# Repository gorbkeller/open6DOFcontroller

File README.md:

# open6DOFcontroller
## Gordon Keller
### 10/23/21

*** An open-source 6DOF (Degrees Of Freedom) controller. ***

This project leverages several different packages to enable 6DOF input akin to the closed-source/proprietary hardware 3D Connexion SpaceMouse.

In this original form, it combines:
* FIRMWARE: The QMK Firmware project (link) -- TBD
* ELECTRONICS: KiCAD (link)
* HARDWARE/MODELS: Autodesk Fusion360 (link), though intention to eventually port to FreeCAD.

This controller is based on hall-effect sensors. The first pass of algorithms developed to convert magnetic signals to 6DOF aren't very sophistocated and could use a major rework.
Theoretically, it can be used to control any 3D virtualized perspective/object. Eventually, I want to use it to fly the Lynchpin drone (link) in simulation and in IRL too ;)
I've included in this first installment a driver written for Fusion360 camera view control as an example useage. This is written using the Fusion360 Scripting API.

The outputs of the one-handed module are given in either XYZ-translation + WIJK-Quaternion ("pose-mode") or XYZ-translation + Roll/Pitch/Yaw ("euler-mode"). 

Some people might not like the 6DOF with one hand control, so a fork of this repo (3DOF-3DOF) should be created eventually which splits the device in two for use with both hands. This method involves less signal processing but requires multiple PCBs.

In-depth plan TBD! - gribgrob_k

[The main bodies of the V0.1 design](imgs/o6DOFc_V0.1.png)

TO-DO:
High-priority:
1. Validate first version of the flex PCB
2. Finish start-up calibration sequence
3. Port data processing to fusion script for proof-of-concept

Low-priority:
1. Port output values from example Fusion script to the dedicated MCU (arduino initially)
2. Develop QMK-side of the device

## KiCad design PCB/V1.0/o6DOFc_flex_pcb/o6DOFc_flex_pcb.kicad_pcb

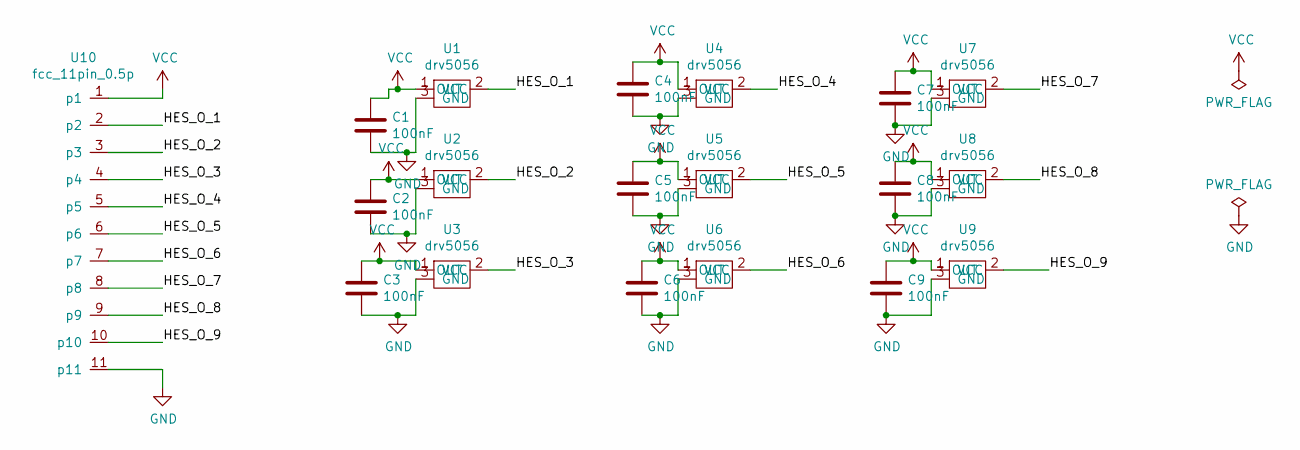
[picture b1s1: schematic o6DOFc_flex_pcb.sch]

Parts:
C1, C2, C3, C4, C5, C6, C7, C8, C9: 100nF; C_0603_1608Metric
U1, U2, U3, U4, U5, U6, U7, U8, U9: drv5056; SOT-23
U10: fcc_11pin_0.5p; ffc_11_pin_0.5_p

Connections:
/HES_O_1: U1.2 (OUT), U10.2 (p2)
/HES_O_2: U2.2 (OUT), U10.3 (p3)
/HES_O_3: U3.2 (OUT), U10.4 (p4)
/HES_O_4: U4.2 (OUT), U10.5 (p5)
/HES_O_5: U5.2 (OUT), U10.6 (p6)
/HES_O_6: U6.2 (OUT), U10.7 (p7)
/HES_O_7: U7.2 (OUT), U10.8 (p8)
/HES_O_8: U8.2 (OUT), U10.9 (p9)
/HES_O_9: U9.2 (OUT), U10.10 (p10)
GND: C1.2, C2.2, C3.2, C4.2, C5.2, C6.2, C7.2, C8.2, C9.2, U1.3 (GND), U2.3 (GND), U3.3 (GND), U4.3 (GND), U5.3 (GND), U6.3 (GND), U7.3 (GND), U8.3 (GND), U9.3 (GND), U10.11 (p11)
VCC: C1.1, C2.1, C3.1, C4.1, C5.1, C6.1, C7.1, C8.1, C9.1, U1.1 (VCC), U2.1 (VCC), U3.1 (VCC), U4.1 (VCC), U5.1 (VCC), U6.1 (VCC), U7.1 (VCC), U8.1 (VCC), U9.1 (VCC), U10.1 (p1)

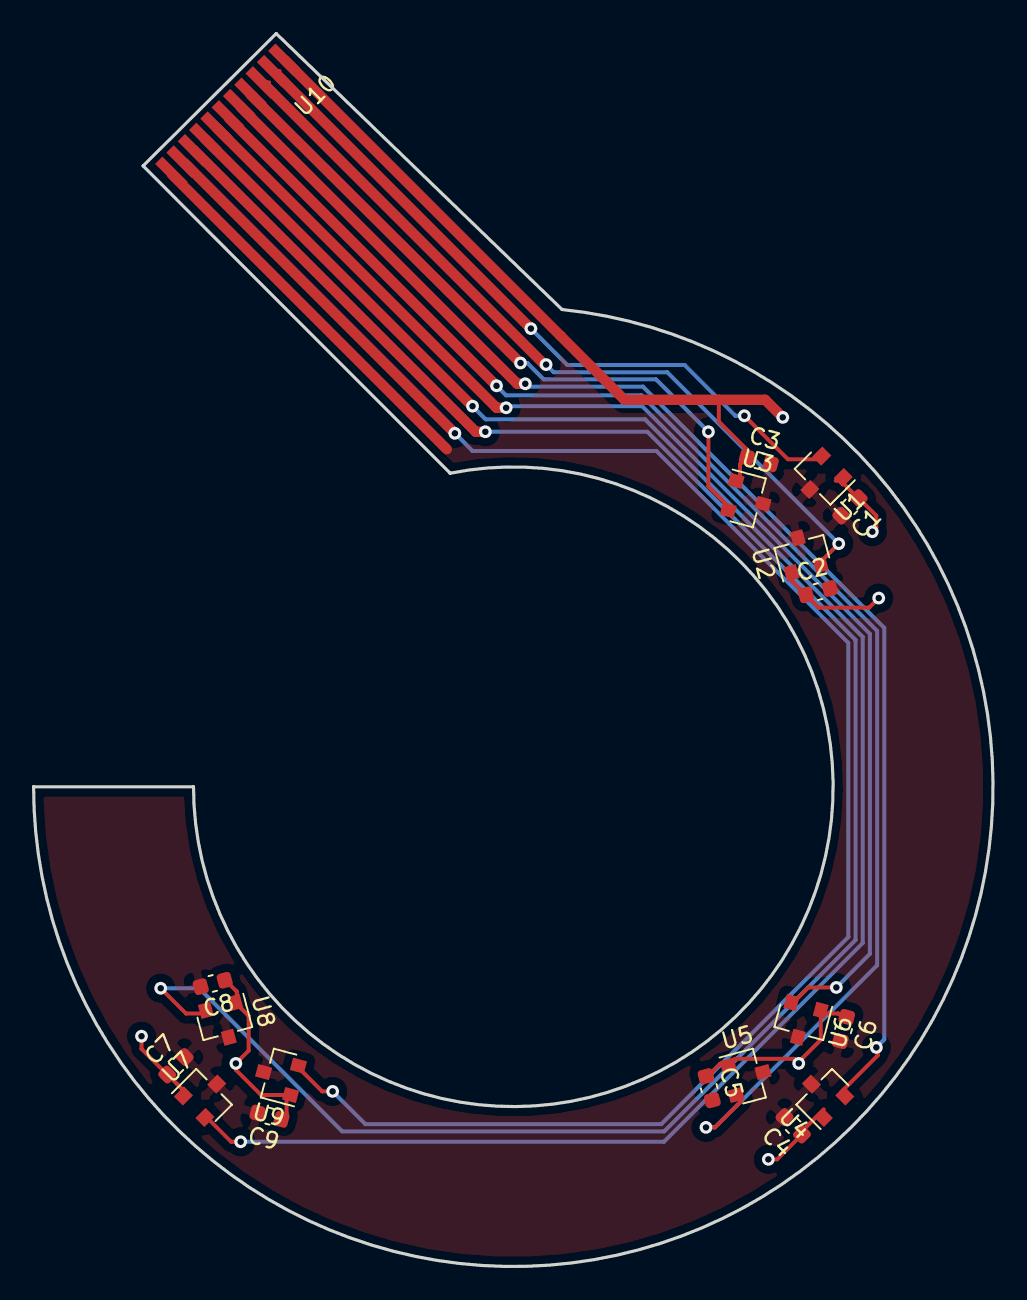
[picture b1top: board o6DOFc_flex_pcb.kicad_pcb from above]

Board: 2 copper layers, 60.0 x 77.1 mm, 19 parts (0 on the bottom side), 11 nets.

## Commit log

2021-10-23 Added details to the READMEw
2021-10-23 Added Fusion360 example driver
2021-10-23 Added image of the basic bodies to the readme
2021-10-23 Added the V0.0 stls
2021-10-23 Fixed link to image
2021-10-23 Added v0.1 STLs
2021-10-23 Added super basic script for reading out values from HEFs
2021-10-23 made the readme less obnoxious
2021-10-23 Uploading initial KiCAD project
2021-10-23 Moved calibration and testing files to a new direcotry
2021-10-23 added the Fusion360 sample driver for adjusting camera positionw
2021-10-31 added first variant of the 9-sensor flex PCB
2021-10-31 Updated to-dos to reflect first edition of the flex pcb done
